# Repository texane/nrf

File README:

NORDIC chipsets related repository

nrf24l01p and nrf905 are currently supported. There is an implem for
nrf2401a, not tested.

This repo contains:
. microcontroller code to use the NRF chipsets (refer to src directory),
. host library to communicate with the chipset from LINUX over serial
(refer to snrf/src directory),
. schematics for a serial bridge board (refer to snrf/hw directory).

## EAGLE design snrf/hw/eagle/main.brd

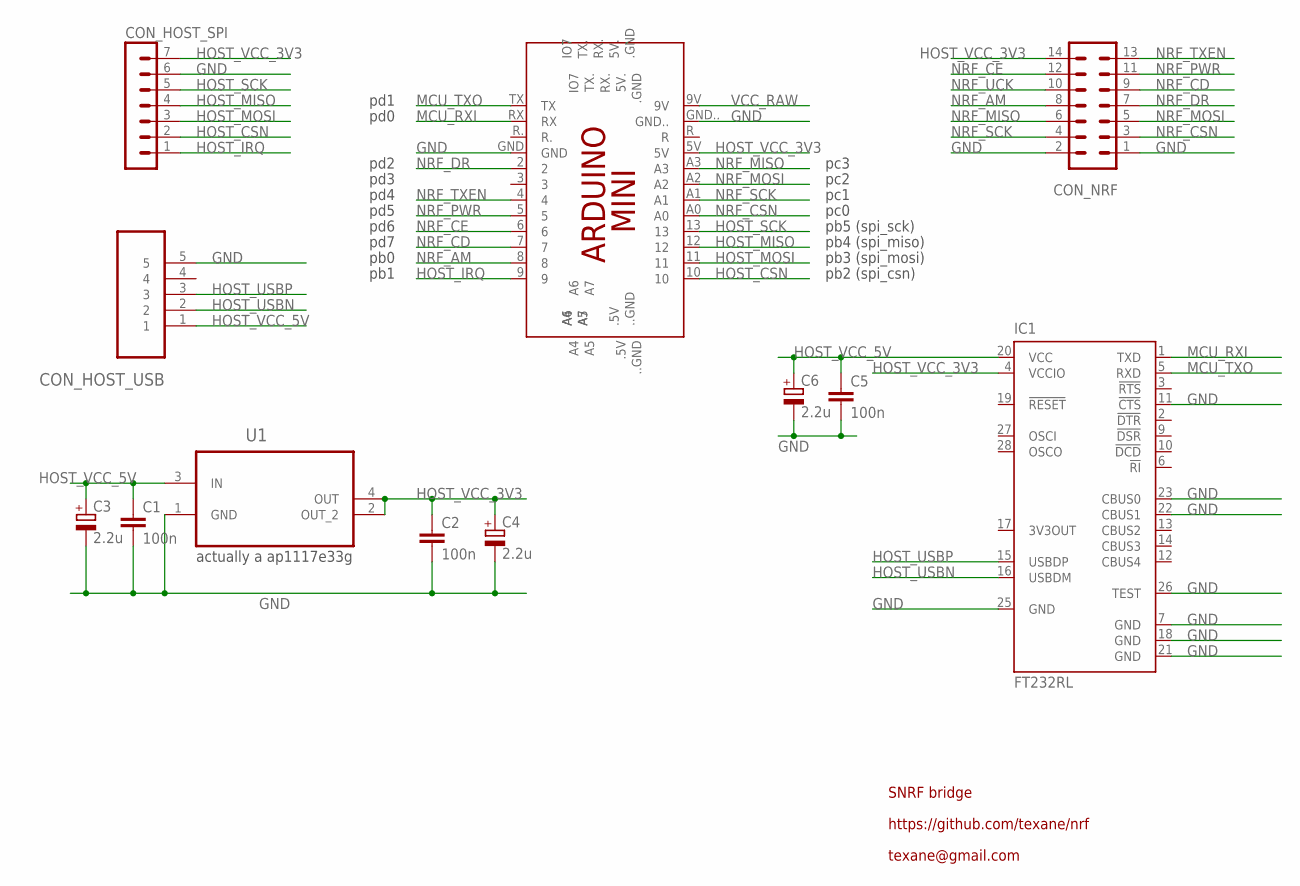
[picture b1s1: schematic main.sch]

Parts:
C1, C2, C5: 100n; C1206K
C3, C4, C6: 2.2u; A/3216-18W
CON_HOST_SPI: MA07-1
CON_HOST_USB: 47346-0001; MOLEX_47346-0001
CON_NRF: MA07-2
IC1: FT232RL; SSOP28
PCB1: ARDUINO_MINI
U1: LDO33; SOT230P700X180-4N

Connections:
GND: C1.2, C2.2, C3.-, C4.-, C5.2, C6.-, CON_HOST_SPI.6, CON_HOST_USB.5, CON_NRF.1, CON_NRF.2, IC1.7 (GND), IC1.11 (!CTS), IC1.18 (GND), IC1.21 (GND), IC1.22 (CBUS1), IC1.23 (CBUS0), IC1.25 (GND), IC1.26 (TEST), PCB1.GND, PCB1.GND.., U1.1 (GND)
HOST_CSN: CON_HOST_SPI.2, PCB1.10
HOST_IRQ: CON_HOST_SPI.1, PCB1.9
HOST_MISO: CON_HOST_SPI.4, PCB1.12
HOST_MOSI: CON_HOST_SPI.3, PCB1.11
HOST_SCK: CON_HOST_SPI.5, PCB1.13
HOST_USBN: CON_HOST_USB.2, IC1.16 (USBDM)
HOST_USBP: CON_HOST_USB.3, IC1.15 (USBDP)
HOST_VCC_3V3: C2.1, C4.+, CON_HOST_SPI.7, CON_NRF.14, IC1.4 (VCCIO), PCB1.5V, U1.2 (OUT_2), U1.4 (OUT)
HOST_VCC_5V: C1.1, C3.+, C5.1, C6.+, CON_HOST_USB.1, IC1.20 (VCC), U1.3 (IN)
MCU_RXI: IC1.1 (TXD), PCB1.RX
MCU_TXO: IC1.5 (RXD), PCB1.TX
NRF_AM: CON_NRF.8, PCB1.8
NRF_CD: CON_NRF.9, PCB1.7
NRF_CE: CON_NRF.12, PCB1.6
NRF_CSN: CON_NRF.3, PCB1.A0
NRF_DR: CON_NRF.7, PCB1.2
NRF_MISO: CON_NRF.6, PCB1.A3
NRF_MOSI: CON_NRF.5, PCB1.A2
NRF_PWR: CON_NRF.11, PCB1.5
NRF_SCK: CON_NRF.4, PCB1.A1
NRF_TXEN: CON_NRF.13, PCB1.4
NRF_UCK: CON_NRF.10
VCC_RAW: PCB1.9V

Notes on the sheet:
pd6
pd7
pb0
pb1
pd5
pd4
pd3
pd2
pd1
pd0
pc3
pc2
pc1
pc0
pb5 (spi_sck)
pb4 (spi_miso)
pb3 (spi_mosi)
pb2 (spi_csn)
actually a ap1117e33g
SNRF bridge
https://github.com/texane/nrf
texane@gmail.com

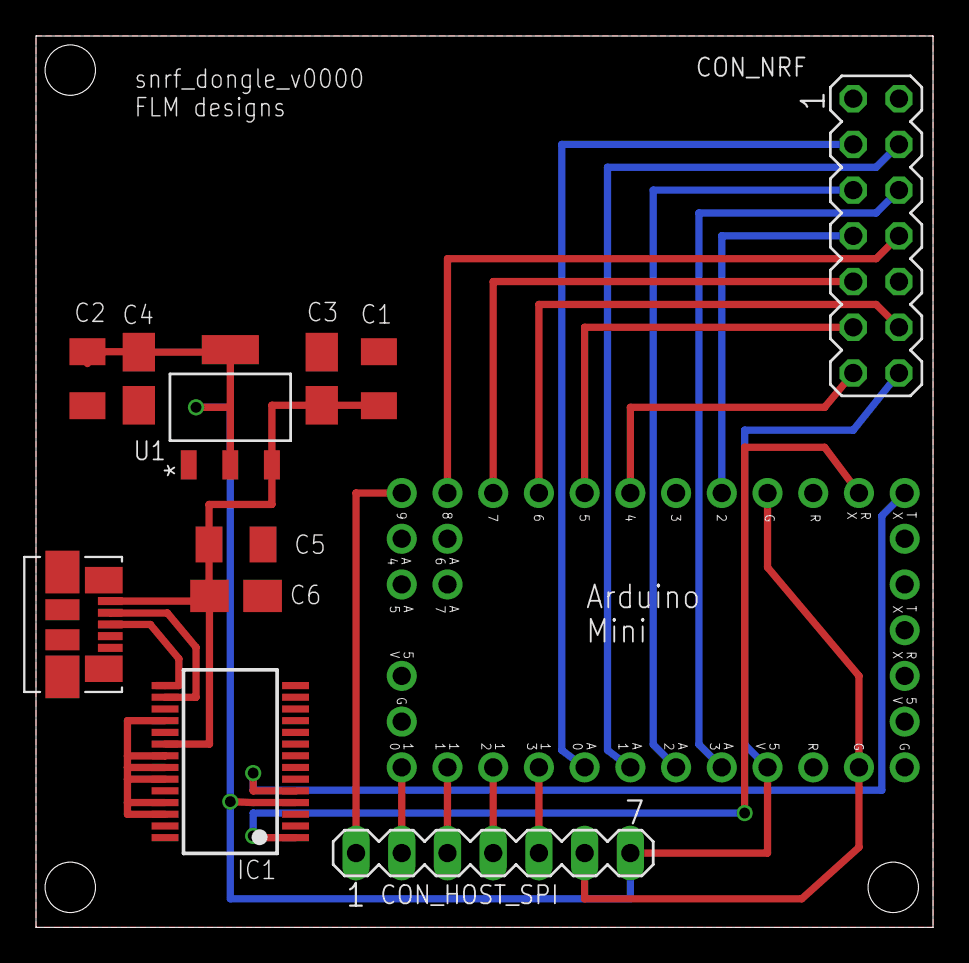
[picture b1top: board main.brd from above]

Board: 2 copper layers, 49.8 x 49.5 mm, 12 parts (0 on the bottom side), 22 nets.

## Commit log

2012-11-04 [ add ] src/atmega328p
2012-11-04 [ update ] sparkfun configuration
2012-11-04 [ update ] wip, working with sparkfun serial board as emitter
2012-11-04 [ fix ] nrf24l01_read_rx_fifo
2012-11-04 [ wip ] tx mode not working
2012-11-05 [ wip ] TODOS
2012-11-05 [ update ] more routines. tx still not working.
2012-11-05 [ fix, wip ] invalid tx irq mask
2012-11-05 [ fix ] nrf24l01p_write_tx has to write twice
2012-11-05 [ update ] write_tx code factorization
2012-11-06 [ update ] TODOs
2012-11-06 [ update ] nrf24l01p_clear_irqs
2012-11-06 [ fix ] deselecting the chip needed, esp. when writing tx fifo.
2012-11-08 [ update ] uart_read_uint8
2012-11-08 [ add ] separate rx, tx sides. add common directory.
2012-11-09 [ update ] add counter to transmit size. use 32 bytes payloads, 3 bytes addr, disable crc
2012-11-09 [ add ] move nrf24l01p spi related routine into spi.c
2012-11-09 [ todo ] implement send_tx_reuse
2012-11-09 [ update ] looping construct adds 3 insns to wait_50us, thus remove 3 nops
2012-11-09 [ rename ] rx,tx to bw/rx,bw/tx (bw for bandwidth)
2012-11-09 [ rename ] main.c to simple/main.c
2012-11-09 [ add ] nrf2401a.c, not compiled
2012-11-09 [ update ] spi_write_uint16
2012-11-09 [ update ] move spi_cs_xxx into nrf24l01p
2012-11-09 [ update ] protect spi.c against multiple inclusions
2012-11-09 [ update ] add audio/rx
2012-11-09 [ update ] use dac7554
2012-11-09 [ update ] implement fifo_read_uint8
2012-11-10 [ update ] extend for 12 bits dac
2012-11-10 [ add ] audio/tx
2012-11-10 [ fix ] assert cs high before initializing spi master
2012-11-10 [ update ] audio tx interrupt handler frequency is 1.25khz (40/32)
2012-11-10 [ add ] audio/sin
2012-11-10 [ update ] audio/tx, sample_array
2012-11-10 [ update ] audio/tx sample array comment
2012-11-10 [ fix ] spi must set DDRB2 as output, cf comment
2012-11-10 [ update ] dac7554 uses spi_xxx_cpol
2012-11-10 [ update ] use portd2 for spi cs
2012-11-10 [ update, rename ] rename sin to tone, add script and generated files
2012-11-10 [ add ] audio/play speaker test program
2012-11-10 [ update ] rx initialization sequence
2012-11-10 [ update ] use generated files as sample array
2012-11-10 [ update ] spi initialization outside nrf24l01p
2012-11-12 [ update ] bw, check mode
2012-11-14 [ update ] play/main.c, tone_40000_1000
2012-11-14 [ update ] upload scripts use different /dev/ttyACM
2012-11-14 [ fix ] nrf24l01p_cmd_len set after nrf24l01p_flush_rx
2012-11-14 [ update ] audio/rx larger fifo size, lock spi. todo: software spi
2012-11-14 [ update ] audio/tx add internal, unused nrf24l01p_xxx routines
2012-11-14 [ update ] dac7554, softspi
2012-11-14 [ update ] optimize fifo index arithmetic according to buffer size
2012-11-14 [ update ] nrf24l01p zero copy tx routines
2012-11-14 [ update ] use fifo_write_payload
2012-11-14 [ update ] nrf24l01p zero copy rx routines
2012-11-15 [ wip ] adc.c
2012-11-15 [ update ] implement adc
2012-11-15 [ update, wip ] use adc in tx
2012-11-15 [ update, wip ] adc, disable digital inputs for reduced power consumption
2012-11-15 [ fix ] missing adc ADSC bit
2012-11-15 [ update ] fadc to 1mhz
2012-11-15 [ update ] CONFIG_SIZEOF_SAMPLE
2012-11-16 [ update ] shift 10 bits sample to 12 bits
2012-11-17 [ update, fix ] adc, reference voltage, 10 bits mask
2012-11-17 [ update ] spi, remove spi_write_uint8 nops
2012-11-17 [ update ] nrf24l01p, completion routine, 16 bits payload
2012-11-18 [ add ] doc/pics/scaled
2012-11-18 [ add ] audio/doc/vids
2012-11-19 [ add ] SAM_1296.mpeg
2012-11-20 [ add ] SAM_1294.mpeg
2012-11-21 [ add ] audio/tx/adc8327.c
2012-11-21 [ update ] adc8327 wip
2012-11-21 [ add ] softspi
2012-11-21 [ update ] make adc8327 compile
2012-11-21 [ update ] softspi, comment
2012-11-22 [ update ] adc8327
2012-11-22 [ add ] audio/adc8327 unit test. wip.
2012-11-24 [ update ] minor: add commented non shifted adc_read()
2012-11-24 [ add ] sch/npn_darlington
2012-11-24 [ update ] rx, CONFIG_USE_UART
2012-11-24 [ add ] vids/SAM_1316.mpeg
2012-12-03 [ update ] latest tx setup
2013-11-02 [ add ] range test
2013-11-02 [ add ] range/rx/upload_nano.sh
2013-11-02 [ update ] use 16 bytes pattern
2013-11-02 [ update ] range/rx uses interrupt on change
2013-11-03 [ update ] range/rx, CONFIG_USE_{LED,SLEEP}
2013-11-10 [ add ] snrf
2013-11-10 [ add ] snrf, comments
2013-11-10 [ update ] snrf/host, fifo msg list
2013-11-10 [ update ] debug msg, info key
2013-11-10 [ update ] wait_msg_n
2013-11-10 [ add ] snrf/src/dev, not compiling yet
2013-11-10 [ update ] snrf/src/dev compiling, to be tested
2013-11-10 [ update ] snrf host main program, simple command interpreter
2013-11-11 [ fix ] disable hardware flow control
2013-11-11 [ fix ] serial conf missing field, union packing bug, missing COMPL
2013-11-11 [ update ] snrf dev, process messages sequentially in main
2013-11-11 [ update ] snrf_sync
2013-11-11 [ revert ] previous range/tx commit
2013-11-11 [ add ] snrf host_cli
2013-11-11 [ update ] snrf host_cli, get_uint32
2013-11-11 [ update, fix ] snrf, implement GET operation. fix payload width setting operation.
2013-11-11 [ update ] host_cli, key val translations
2013-11-11 [ update ] snrf host_cli, read count
2013-11-11 [ add ] dev_node
2013-11-11 [ update ] dev_node, default timer to 1 second
2013-11-12 [ update ] uart_read_uint8 returns an error
2013-11-12 [ update ] snrf, wait msg timeout and resync
2013-11-12 [ update ] snrf, snrf_get_pending_msg
2013-11-12 [ update ] snrf, snrf_read_msg does not block, uses internal buffer. remove snrf_is_pending_msg and use snrf_get_pending_msg return value
2013-11-12 [ fix ] dev_node, TCCR0B used instead of TCCR1B
2013-11-12 [ fix, update ] timersub leads to negative results. snrf state not updated.
2013-11-12 [ add ] snrf todo
2013-11-12 [ update ] uart finer interrupt handling
2013-11-12 [ update ] write_payload_msg to avoid memory copy
2013-11-12 [ update ] do not disable interrupts until check before sleep. add nrf24l01p_is_rx_irq_noread for this purpose.
2013-11-12 [ update ] nrf24l01p_is_{tx,rx}_irq must only acknowledge source of concern
2013-11-12 [ update ] SNRF_KEY_UART_FLAGS
2013-11-12 [ update ] tcdrain
2013-11-12 [ update ] clear uart errors
2013-11-13 [ fix ] sei before looping. disable interrupts during sync.
2013-11-13 [ rm ] remove audio, moved in nrf_speaker repo
2013-11-13 [ rename ] strip src/atmega328p
2013-11-13 [ add ] README
2013-11-17 [ fix ] synchronize if framing error
2013-11-17 [ fix ] initialize message queue before using messages
2013-11-17 [ update ] more NRF24L01P_IO_IRQ_xxx defines
2013-11-17 [ fix ] NRF24L01P_IO_IRQ_xxx
2013-11-27 [ update ] use CLK_PRESCAL in wait loop
2013-11-27 [ update ] use 4 bytes wide addresses
2013-11-27 [ update ] snrf_open_with_path
2013-11-27 [ mv ] move nrf2401a in common
2013-11-27 [ update ] rename common to src, move units in unit directory
2013-11-27 [ update ] use nrf src instead of common
2014-01-18 [ add ] nrf905 support
2014-01-18 [ add ] doc/notes
2014-01-20 [ update ] doc/notes
2014-01-20 [ fix ] pinout
2014-01-20 [ fix ] tx_nrf905 delay
2014-01-20 [ add ] rx_nrf905
2014-01-20 [ update ] nrf905 atmega328p lm4f120xl factorization
2014-01-20 [ update ] tx_nrf905 atmega328p lm4f120xl factorization
2014-01-20 [ add ] tx_nrf905_lm4f120xl
2014-01-20 [ add, update ] add lm4f120xl spi support
2014-01-21 [ update ] use hostname to set path
2014-01-21 [ fix ] upload_lm4f120xl.sh
2014-01-21 [ fix ] nrf905 defaults to powerdown before first command
2014-01-21 [ update ] SOFTSPI_MODE_0
2014-01-21 [ fix ] nrf905 incorrect config byte offset
2014-01-21 [ fix ] nrf905 use trx_ce, poll dr for transmission
2014-01-22 [ update, fix ] nrf905 config register
2014-01-22 [ add ] nrf905_rx lm4f120 files
2014-01-23 [ update ] nrf905 unit test minor
2014-01-24 [ update ] nrf905, set_payload_width, commit_config
2014-01-26 [ update ] nrf905, 433 range test
2014-01-27 [ add ] nrf905_decoder
2014-02-16 [ add ] minipro_3v3
2014-02-16 [ update ] nrf905, minipro_3v3 support
2014-02-16 [ fix ] tx_nrf905 rx_addr
2014-02-16 [ update, add ] rx_nrf905: minipro_3v3 support, reset pattern before read
2014-02-16 [ update ] rx_nrf905 upload_lm4f120xl.sh, change target for tests
2014-02-16 [ update ] limit uart to 300 bauds if CLK_PRESCAL set
2014-02-17 [ update ] nrf905, zero copy, rx irq pin
2014-02-17 [ update ] nrf wrappers
2014-02-18 [ add ] minipro_3v3 files
2014-02-18 [ add ] nrf abstract layer
2014-02-18 [ update ] snrf dev uses nrf abstract layer
2014-02-18 [ update ] README
2014-02-18 [ update ] nrf_get_{tx,rx}_addr
2014-02-18 [ update ] SNRF_KEY_NRF_CHIPSET
2014-02-18 [ update ] dev_node unit uses nrf abstract layer
2014-02-18 [ update ] nrf_read_payload_zero
2014-02-18 [ update ] nrf_send_payload_zero
2014-02-18 [ add ] minipro_3v3 build files
2014-02-18 [ fix, update ] fix nrf905_read_config, update nrf abstract layer
2014-02-19 [ fix, update ] unit test timer. nrf default setup.
2014-02-22 [ fix ] nrf905_clear_trx to leave in standby mode
2014-03-09 [ update ] set nrf905 pa_pwr to -10db
2014-03-30 [ fix ] sync on first get state error
2014-03-30 [ fix ] set nrf905 to rx mode after write
2014-03-30 [ fix ] payload write automaton
2014-04-10 [ update ] set SNRF_MAX_PAYLOAD_WIDTH to 24
2014-04-17 [ update ] makefile uses CROSS_COMPILE
2014-04-18 [ add ] hw/dongle
2014-04-18 [ update ] schematics done, board routed. nrf connector has to be moved for fitting
2014-04-19 [ update ] rerouted to fit nrf board
2014-04-19 [ update ] clean tNames
2014-04-19 [ update ] add name and version
2014-04-19 [ update ] change minipro silkscreen to tDocu
2014-04-19 [ add ] dongle, schematics pdf
2014-04-19 [ update ] dongle bom ftdi chipset ref
2014-05-02 [ update ] fix softspi miso mode. nrf905 can use softspi, pins definable.
2014-05-02 [ update ] snrf eagle schematics, frame added
2014-05-02 [ add ] main.hex
2014-05-02 [ add ] pics
2014-05-02 [ update ] schematics
2014-05-06 [ update ] default power to max
